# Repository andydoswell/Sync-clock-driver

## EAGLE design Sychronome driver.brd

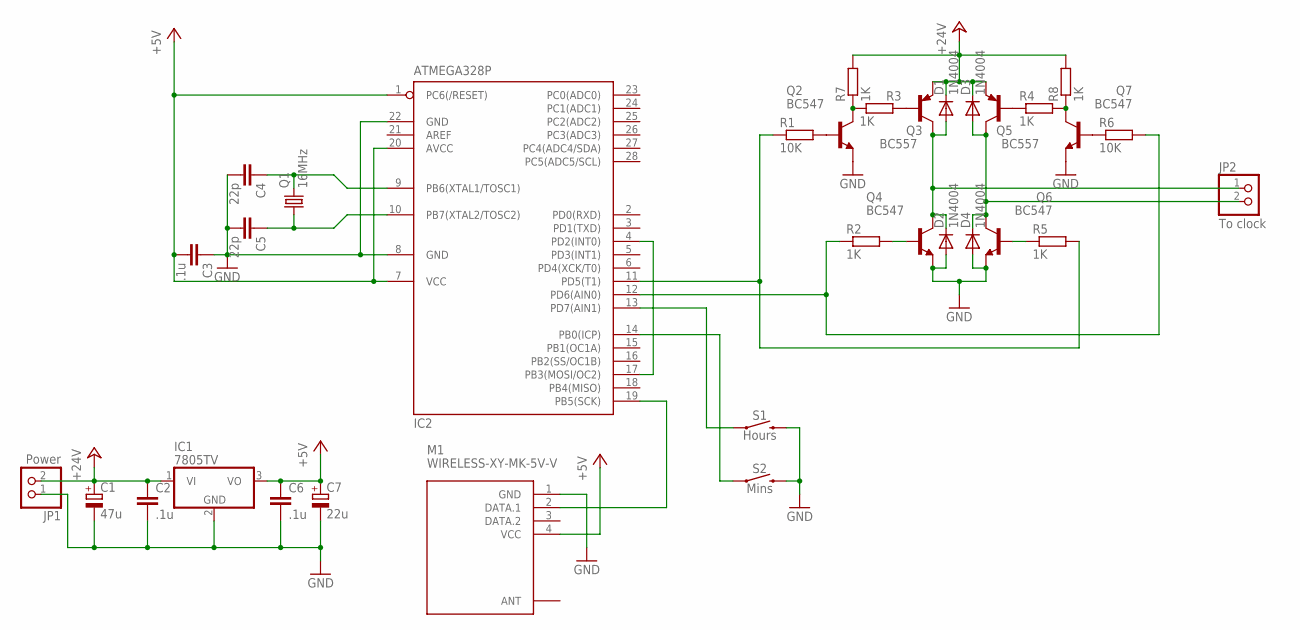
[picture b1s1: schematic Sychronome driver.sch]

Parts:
C1: 47u; E2,5-7
C2, C3, C6: .1u; C025-024X044
C4, C5: 22p; C025-024X044
C7: 22u; E2,5-7
D1, D2, D3, D4: 1N4004; DO41-10
IC1: 7805TV; TO220V
IC2: ATMEGA328P; DIL28-3
JP1: Power; 1X02
JP2: To clock; 1X02
M1: WIRELESS-XY-MK-5V-V; WIRELESS-XY-MK-5V#V
Q1: 16MHz; HC49U-V
Q2, Q4, Q6, Q7: BC547; TO92
Q3, Q5: BC557; TO92
R1, R6: 10K; 0204/7
R2, R3, R4, R5, R7, R8: 1K; 0204/7
S1: Hours; TACTILE_SWITCH_PTH_6.0MM
S2: Mins; TACTILE_SWITCH_PTH_6.0MM

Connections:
+5V: C3.2, C6.1, C7.+, IC1.3 (VO), IC2.1 (PC6(/RESET)), IC2.7 (VCC), IC2.20 (AVCC), M1.4 (VCC)
+24V: C1.+, C2.1, D1.C, D3.C, IC1.1 (VI), JP1.2, Q3.1 (E), Q5.1 (E), R7.2, R8.2
GND: C1.-, C2.2, C3.1, C4.2, C5.2, C6.2, C7.-, D2.A, D4.A, IC1.2 (GND), IC2.8 (GND), IC2.22 (GND), JP1.1, M1.1 (GND), Q2.1 (E), Q4.1 (E), Q6.1 (E), Q7.1 (E), S1.3 (2), S2.3 (2)
unnamed: IC2.12 (PD6(AIN0)), R2.1, R6.2
unnamed: IC2.4 (PD2(INT0)), IC2.17 (PB3(MOSI/OC2))
unnamed: IC2.13 (PD7(AIN1)), S1.1
unnamed: IC2.14 (PB0(ICP)), S2.1
unnamed: IC2.19 (PB5(SCK)), M1.2 (DATA.1)
unnamed: D1.A, D2.C, JP2.1, Q3.3 (C), Q4.3 (C)
unnamed: D3.A, D4.C, JP2.2, Q5.3 (C), Q6.3 (C)
unnamed: Q2.2 (B), R1.2
unnamed: Q3.2 (B), R3.2
unnamed: Q5.2 (B), R4.1
unnamed: Q7.2 (B), R6.1
unnamed: Q2.3 (C), R3.1, R7.1
unnamed: Q7.3 (C), R4.2, R8.1
unnamed: IC2.11 (PD5(T1)), R1.1, R5.2
unnamed: Q4.2 (B), R2.2
unnamed: Q6.2 (B), R5.1
unnamed: C4.1, IC2.9 (PB6(XTAL1/TOSC1)), Q1.2
unnamed: C5.1, IC2.10 (PB7(XTAL2/TOSC2)), Q1.1

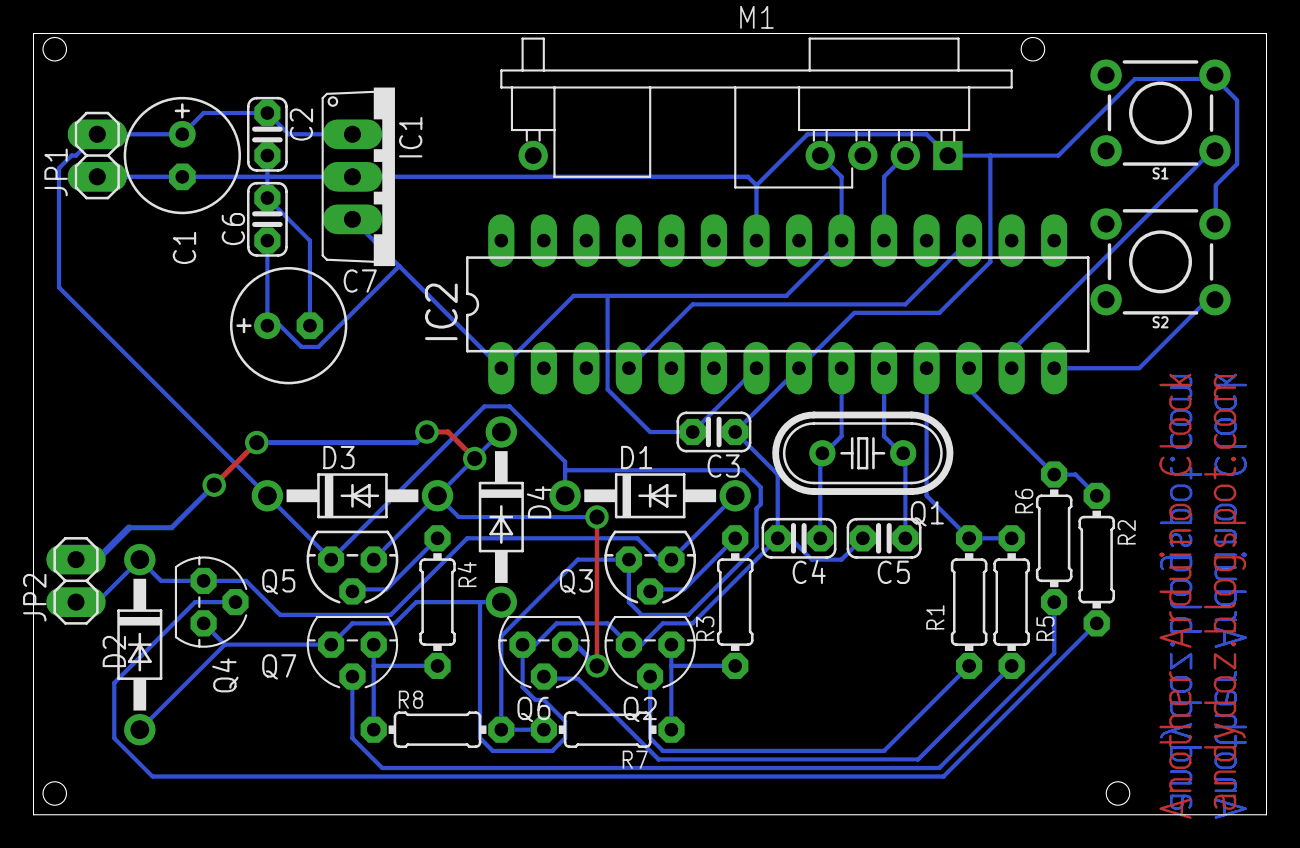
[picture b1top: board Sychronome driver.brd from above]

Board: 2 copper layers, 73.6 x 46.7 mm, 33 parts (0 on the bottom side), 21 nets.

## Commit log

2018-05-19 Create LICENSE
2018-05-19 Add files via upload
    Schematic
2018-05-19 Add files via upload
    Eagle brd file.

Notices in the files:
parts and their libraries:
diy-modules: Released under the Creative Commons Attribution 4.0 International License: http://creativecommons.org/licenses/by/4.0
SparkFun-Switches: Licensing: Creative Commons ShareAlike 4.0 International - https://creativecommons.org/licenses/by-sa/4.0
